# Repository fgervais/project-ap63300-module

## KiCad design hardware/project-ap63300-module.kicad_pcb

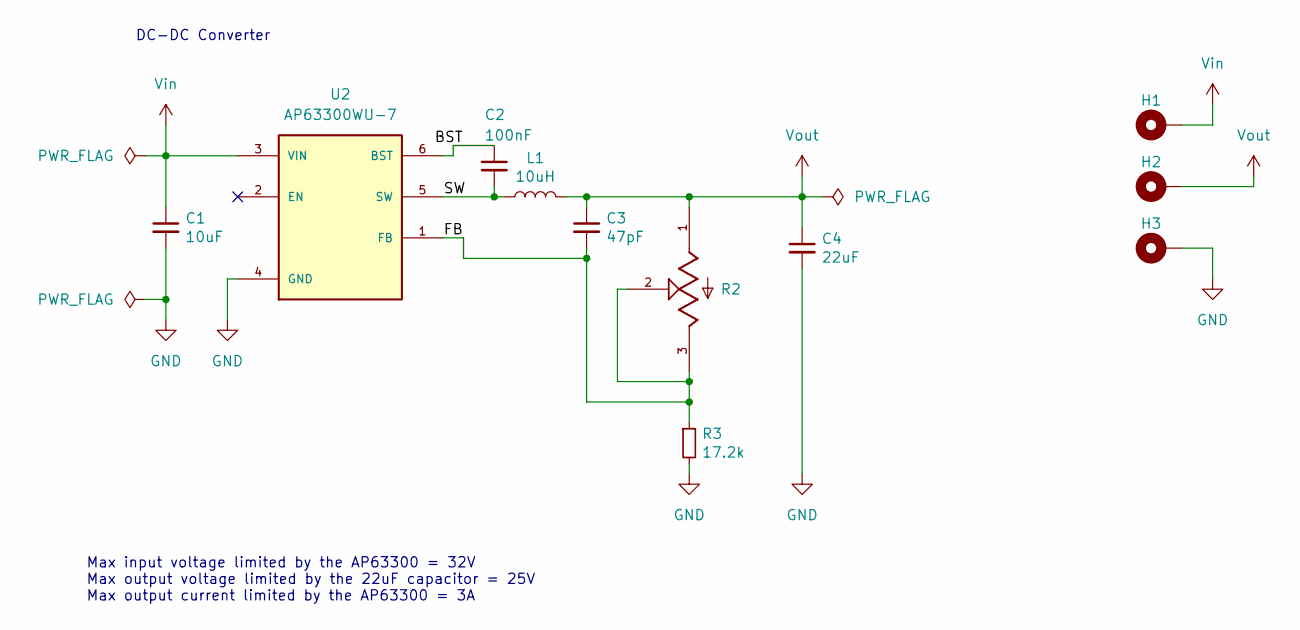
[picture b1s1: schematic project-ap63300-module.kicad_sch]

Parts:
C1: 10uF; C_1210_3225Metric_Pad1.33x2.70mm_HandSolder
C2: 100nF; C_0603_1608Metric
C3: 47pF; C_0603_1608Metric
C4: 22uF; C_1210_3225Metric_Pad1.33x2.70mm_HandSolder
H1, H2, H3: MountingHole_Pad; MountingHole_2.2mm_M2_ISO14580_Pad
L1: 10uH; IND_SPM10040T-100M
R2: TC33X-2-504E; TRIM_TC33X-2-504E
R3: 17.2k; R_0603_1608Metric
U2: AP63300WU-7; SOT95P280X100-6N; PARTREV 2020-04-24

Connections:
/BST: C2.1, U2.6 (BST)
/FB: C3.2, R2.2, R2.3, R3.1, U2.1 (FB)
/SW: C2.2, L1.1, U2.5 (SW)
GND: C1.2, C4.2, H3.1, R3.2, U2.4 (GND)
Vin: C1.1, H1.1, U2.3 (VIN)
Vout: C3.1, C4.1, H2.1, L1.2, R2.1

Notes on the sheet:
Max input voltage limited by the AP63300 = 32V Max output voltage limited by the 22uF capacitor = 25V Max output current limited by the AP63300 = 3A
DC-DC Converter

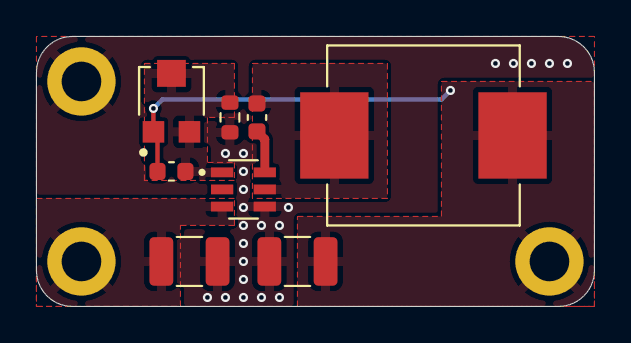
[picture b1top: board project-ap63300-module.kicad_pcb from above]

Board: 2 copper layers, 31.0 x 15.0 mm, 11 parts (0 on the bottom side), 6 nets.

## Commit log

2021-04-11 First commit of the AP63300 module
2025-01-04 Remove the Blink submodule
2025-01-04 Open with kicad 8
2025-01-04 Make AP63300 schematic variable
2025-01-04 sch: add mounting holes
2025-01-04 Ignore backups
2025-01-05 pcb: first placement
2025-01-05 pcb: first routing draft
2025-01-05 Add labels
2025-01-05 Update exclusions
2025-01-05 pcb: move labels
    To work around font size bug.
2025-01-30 Add assembly file
2025-01-31 Add overview image
